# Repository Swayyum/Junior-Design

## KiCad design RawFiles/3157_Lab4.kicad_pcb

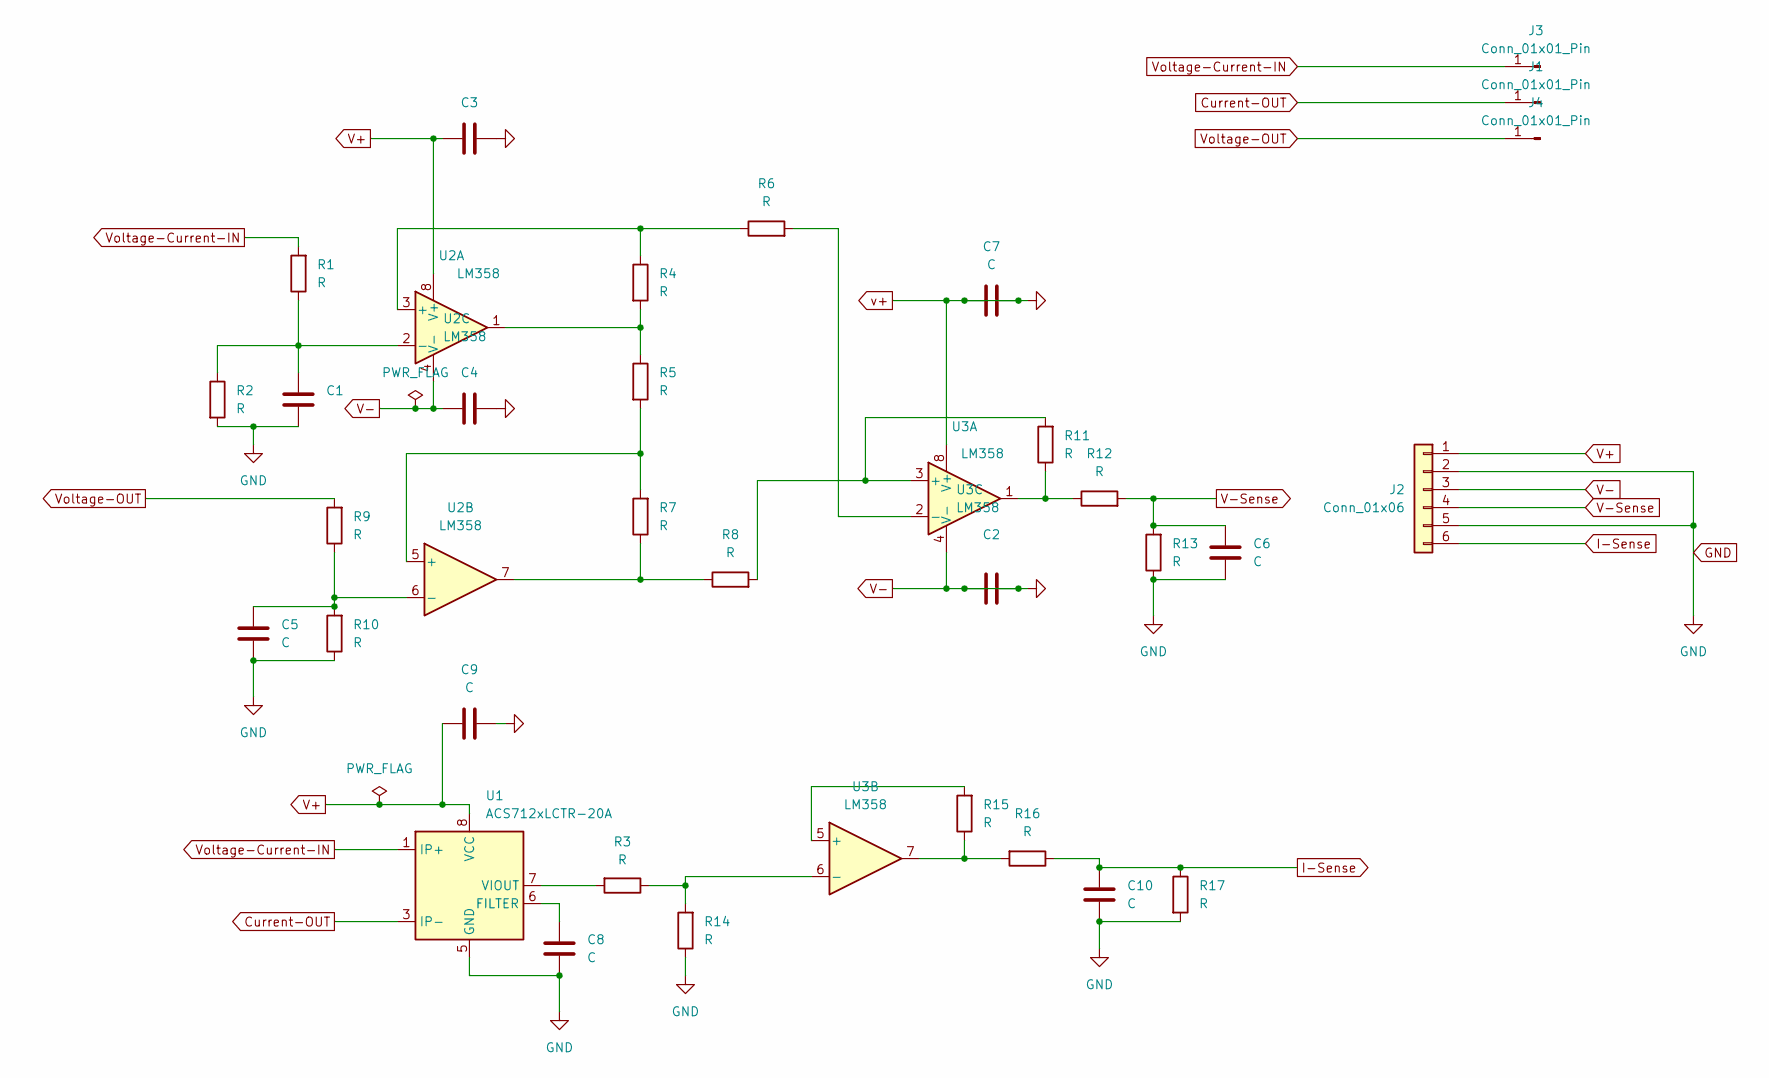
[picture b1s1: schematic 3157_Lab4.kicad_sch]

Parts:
C1, C2, C3, C4, C5, C6, C7, C8, C9, C10: C; C_0603_1608Metric_Pad1.08x0.95mm_HandSolder
J1, J3, J4: Conn_01x01_Pin; Pin_D0.7mm_L6.5mm_W1.8mm_FlatFork
J2: Conn_01x06; JST_XH_B6B-XH-A_1x06_P2.50mm_Vertical
R1, R2, R3, R4, R5, R6, R7, R8, R9, R10, R11, R12, R13, R14, R15, R16, R17: R; R_0603_1608Metric_Pad0.98x0.95mm_HandSolder
U1: ACS712xLCTR-20A; SOIC-8_3.9x4.9mm_P1.27mm
U2, U3: LM358; DIP-8_W7.62mm

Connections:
Current-OUT: J1.1, U1.3 (IP-), U1.4 (IP-)
I-Sense: C10.2, J2.6, R16.1, R17.1
unnamed: R4.2, R5.1, U2.1
unnamed: R7.1, R8.1, U2.7
unnamed: R11.1, R12.1, U3.1
unnamed: R15.1, R16.2, U3.7
unnamed: C8.2, U1.6 (FILTER)
unnamed: R3.2, U1.7 (VIOUT)
unnamed: R4.1, R6.1, U2.3 (+)
unnamed: C1.1, R1.1, R2.1, U2.2 (-)
unnamed: R5.2, R7.2, U2.5 (+)
unnamed: C5.1, R9.1, R10.2, U2.6 (-)
unnamed: R8.2, R11.2, U3.3 (+)
unnamed: R6.2, U3.2 (-)
unnamed: R15.2, U3.5 (+)
unnamed: R3.1, R14.2, U3.6 (-)
V-Sense: C6.2, J2.4, R12.2, R13.2
Voltage-Current-IN: J3.1, R1.2, U1.1 (IP+), U1.2 (IP+)
Voltage-OUT: J4.1, R9.2

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
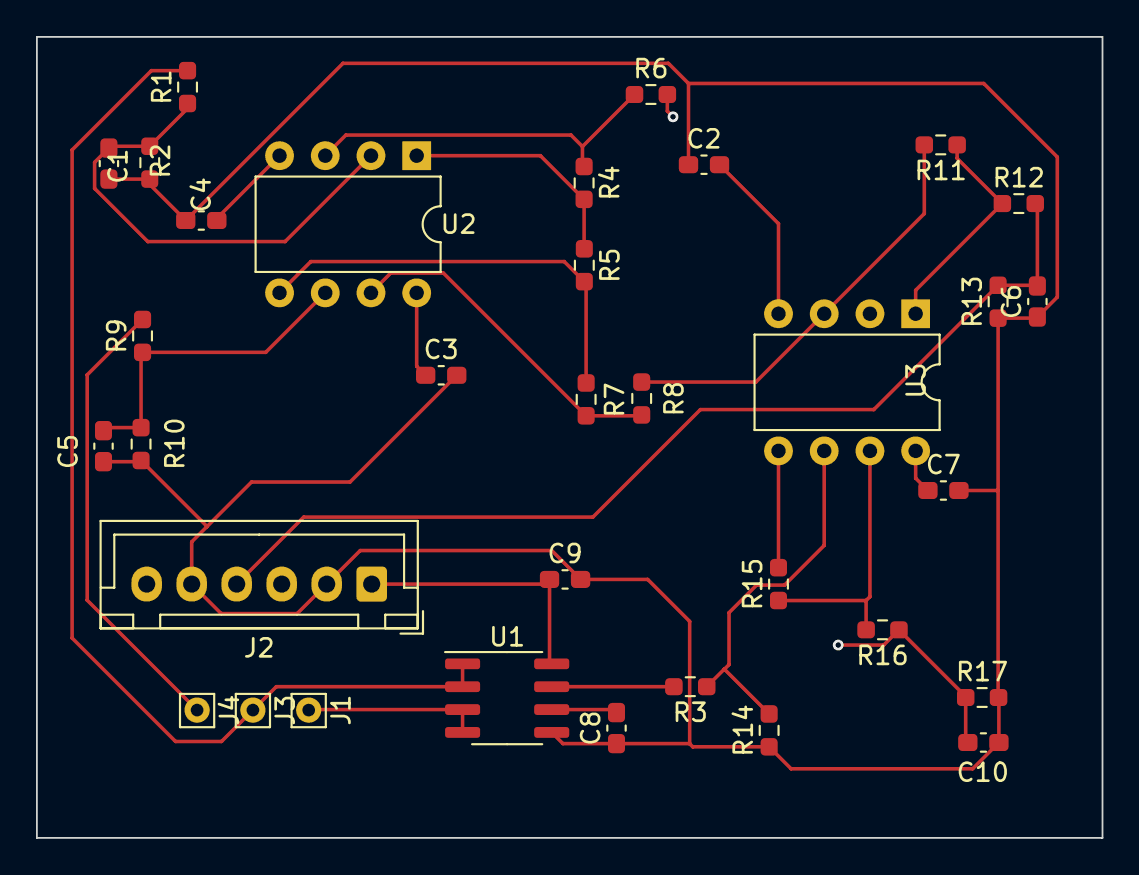
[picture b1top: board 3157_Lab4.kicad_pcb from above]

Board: 4 copper layers, 59.2 x 44.5 mm, 34 parts (0 on the bottom side), 22 nets.

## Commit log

2023-11-19 Create Simulink-PCB
2023-11-19 Create Reports
